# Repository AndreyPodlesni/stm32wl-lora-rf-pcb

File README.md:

# STM32WL LoRa RF PCB (KiCad)

## Overview
This is a 4-layer PCB design of a LoRa sensor node based on the STM32WLE5CCU6.  
It includes a temperature and humidity sensor (HDC2022) and an RF path to an SMA antenna.  
The board was designed in KiCad with focus on a working hardware setup and easy bring-up.  
The RF section follows the STM32WL development board schematics and layout guidelines.

---

## PCB Layout

---

## Key Features  
- STM32WLE5CCU6 (LoRa MCU)  
- HDC2022 temperature & humidity sensor  
- SMA antenna interface  
- 4-layer PCB  
- Battery powered (CR123A)  
- SWD debug interface + UART pins  

---

## Hardware Blocks  
  
### MCU  
STM32WLE5CCU6 with integrated Sub-GHz radio (LoRa).  
Combines MCU and RF transceiver in a single chip, reducing external components and simplifying the design.  

---

### RF Path  
- RF output from the MCU is routed through a matching network to an SMA antenna  
- RF routing implemented as a 50Ω microstrip based on PCB stackup calculations  
- Matching network includes optional components for antenna tuning  

---

### Sensor  
HDC2022 connected over I²C for temperature and humidity measurement  

---

### Battery  
CR123A lithium battery used as the main power source  

Selected for its ability to handle LoRa transmission current peaks and provide reliable long-term operation in a low-duty-cycle system  

Estimated battery life is over 2 years, based on power estimation using STM32CubeMX Power Consumption Calculator  

---

### Debug  
SWD interface and UART pins for programming and debugging  

---

## RF Notes
- RF traces routed as 50Ω controlled impedance  
- Microstrip routing over solid ground plane  
- RF path kept on a single layer (no vias)  

---

## Design Notes
- Matching network allows antenna tuning during testing  
- Battery selected to support LoRa current peaks  
- Power path prevents back-powering during debugging  

---
## Future Improvements
- Refine RF impedance control by considering copper pour clearance and surrounding geometry
- Improve sensor placement to reduce thermal influence from other components
- Further layout optimization for production readiness

## Tools
- KiCad 9  

---

## License
MIT

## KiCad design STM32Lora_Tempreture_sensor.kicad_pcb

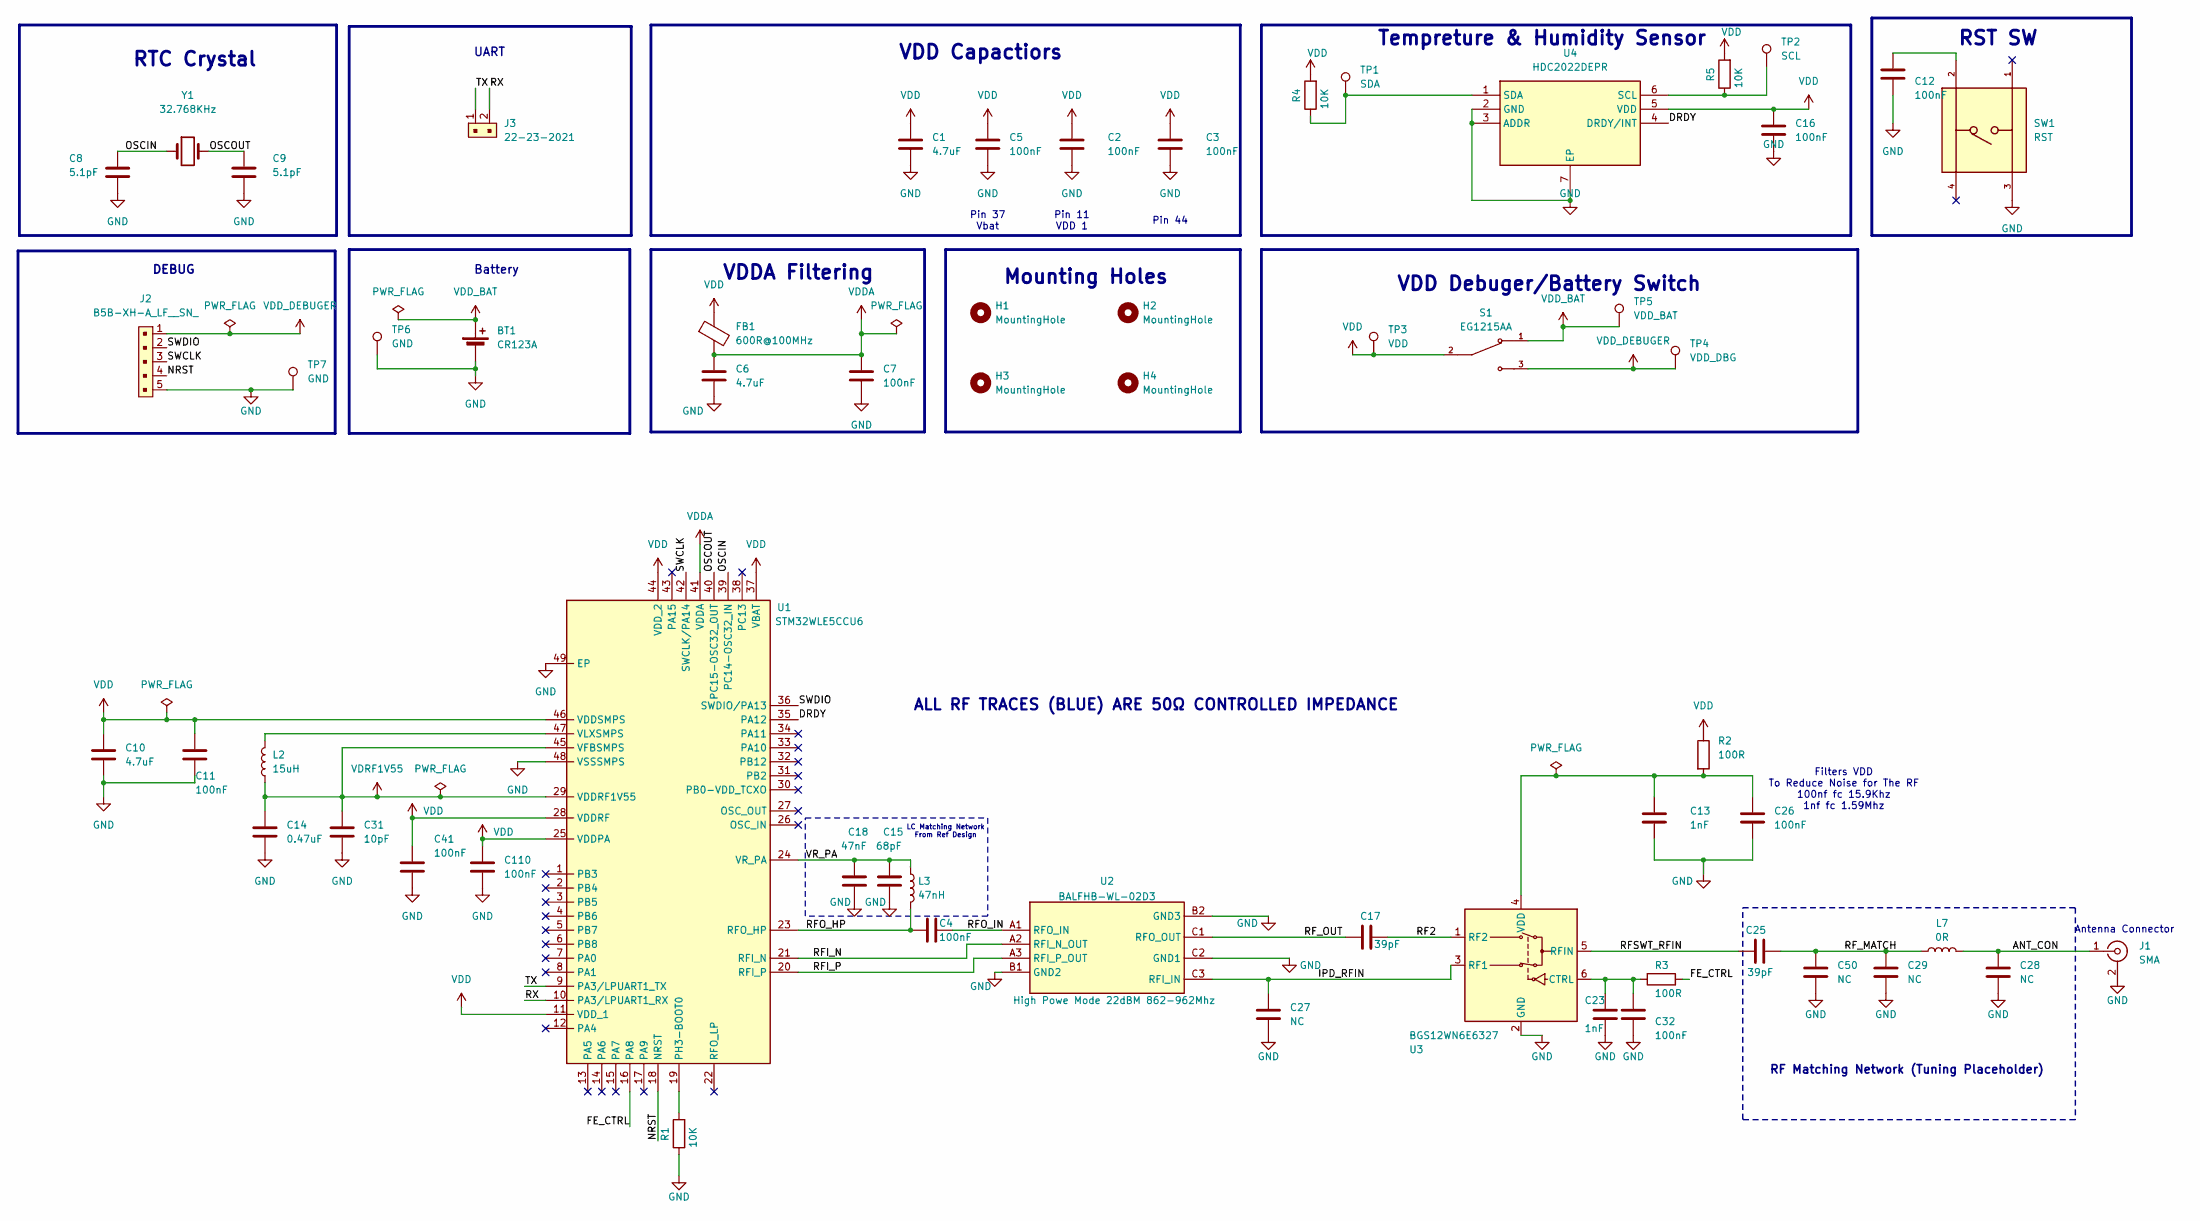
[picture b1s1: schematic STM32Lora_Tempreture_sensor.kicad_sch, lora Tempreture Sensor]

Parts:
BT1: CR123A; BAT_1050
C1, C6, C10: 4.7uF; C_0603_1608Metric
C2, C3, C4, C5, C7, C11, C12, C16, C26, C32, C41, C110: 100nF; C_0402_1005Metric
C8, C9: 5.1pF; C_0402_1005Metric
C13, C23: 1nF; C_0201_0603Metric
C14: 0.47uF; C_0603_1608Metric
C15: 68pF; C_0402_1005Metric
C17, C25: 39pF; C_0201_0603Metric
C18: 47nF; C_0402_1005Metric
C27, C28, C29, C50: NC; C_0201_0603Metric
C31: 10pF; C_0201_0603Metric
FB1: 600R@100MHz; BEADC1608X95N
H1, H2, H3, H4: MountingHole; MountingHole_2.2mm_M2_ISO14580
J1: SMA; SAMTEC_SMA-J-P-H-ST-EM1
J2: B5B-XH-A_LF__SN_; PinHeader_1x5_P2.5mm_Drill1.1mm; MPN B5B-XH-A(LF)(SN); Digi-Key_PN 455-2270-ND
J3: 22-23-2021; PinHeader_1x2_P2.54mm_Drill1.02mm; MPN 22-23-2021; Digi-Key_PN WM4200-ND
L2: 15uH; L_0805_2012Metric
L3: 47nH; L_0402_1005Metric
L7: 0R; L_0201_0603Metric
R1, R4, R5: 10K; R_0603_1608Metric
R2: 100R; R_0201_0603Metric
R3: 100R; R_0201_0603Metric_Pad0.64x0.40mm_HandSolder
S1: EG1215AA; SW_EG1215AA; PARTREV A
SW1: RST; Switch_Tactile_SMD_6x6mm; PARTREV 1.0
TP1: SDA; TestPoint_Pad_D1.0mm
TP2: SCL; TestPoint_Pad_D1.0mm
TP3: VDD; TestPoint_Pad_D1.0mm
TP4: VDD_DBG; TestPoint_Pad_D1.0mm
TP5: VDD_BAT; TestPoint_Pad_D1.0mm
TP6, TP7: GND; TestPoint_Pad_D1.0mm
U1: STM32WLE5CCU6; QFN50P700X700X60-49N-D; Manufacturer_Part_Number STM32WLE5CCU6; Mouser Part Number 511-STM32WLE5CCU6
U2: BALFHB-WL-02D3; BALFHBWL02D3; Mouser Part Number 511-BALFHB-WL-02D3
U3: BGS12WN6E6327; Infineon_PG-TSNP-6-10_0.7x1.1mm_0.7x1.1mm_P0.4mm
U4: HDC2022DEPR; SON100P300X300X115-7N-D; Mouser Part Number 595-HDC2022DEPR
Y1: 32.768KHz; NX2012SA32768KSTDMUB1

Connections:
/ANT_CON: C28.1, J1.1 (In), L7.2
/DRDY: U1.35 (PA12), U4.4 (DRDY/INT)
/FE_CTRL: R3.1, U1.16 (PA8)
/IPD_RFIN: C27.1, U2.C3 (RFI_IN), U3.3 (RF1)
/OSCIN: C8.1, U1.39 (PC14-OSC32_IN), Y1.1
/OSCOUT: C9.1, U1.40 (PC15-OSC32_OUT), Y1.2
/RF2: C17.2, U3.1 (RF2)
/RFI_N: U1.21 (RFI_N), U2.A2 (RFI_N_OUT)
/RFI_P: U1.20 (RFI_P), U2.A3 (RFI_P_OUT)
/RFO_HP: C4.1, L3.2, U1.23 (RFO_HP)
/RFO_IN: C4.2, U2.A1 (RFO_IN)
/RFSWT_RFIN: C25.1, U3.5 (RFIN)
/RF_MATCH: C25.2, C29.1, C50.1, L7.1
/RF_OUT: C17.1, U2.C1 (RFO_OUT)
/RX: J3.2, U1.10 (PA3/LPUART1_RX)
/SWCLK: J2.3, U1.42 (SWCLK/PA14)
/SWDIO: J2.2, U1.36 (SWDIO/PA13)
/TX: J3.1, U1.9 (PA3/LPUART1_TX)
/VR_PA: C15.1, C18.1, L3.1, U1.24 (VR_PA)
GND: BT1.N (-), C1.2, C2.2, C3.2, C5.2, C6.2, C7.2, C8.2, C9.2, C10.2, C11.2, C12.2, C13.2, C14.2, C15.2, C16.2, C18.2, C23.2, C26.2, C27.2, C28.2, C29.2, C31.2, C32.2, C41.2, C50.2, C110.2, J1.2 (Ext), J2.5, R1.1, SW1.3, TP6.1, TP7.1, U1.48 (VSSSMPS), U1.49 (EP), U2.B1 (GND2), U2.B2 (GND3), U2.C2 (GND1), U3.2 (GND), U4.2 (GND), U4.3 (ADDR), U4.7 (EP)
unnamed: R1.2, U1.19 (PH3-BOOT0)
unnamed: L2.2, U1.47 (VLXSMPS)
unnamed: C23.1, C32.1, R3.2, U3.6 (CTRL)
unnamed: C13.1, C26.1, R2.2, U3.4 (VDD)
unnamed: R5.1, TP2.1, U4.6 (SCL)
unnamed: R4.1, TP1.1, U4.1 (SDA)
VDD: C1.1, C2.1, C3.1, C5.1, C10.1, C11.1, C16.1, C41.1, C110.1, FB1.1, R2.1, R4.2, R5.2, S1.2, TP3.1, U1.11 (VDD_1), U1.25 (VDDPA), U1.28 (VDDRF), U1.37 (VBAT), U1.44 (VDD_2), U1.46 (VDDSMPS), U4.5 (VDD)
VDDA: C6.1, C7.1, FB1.2, U1.41 (VDDA)
VDD_BAT: BT1.P (+), S1.1, TP5.1
VDD_DEBUGER: J2.1, S1.3, TP4.1
VDRF1V55: C14.1, C31.1, L2.1, U1.29 (VDDRF1V55), U1.45 (VFBSMPS)

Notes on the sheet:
Pin 37 Vbat
RTC Crystal
Filters VDD To Reduce Noise for The RF 100nf fc 15.9Khz 1nf fc 1.59Mhz
VDD Debuger/Battery Switch
ALL RF TRACES (BLUE) ARE 50Ω CONTROLLED IMPEDANCE
UART
Pin 44
Antenna Connector
Battery
LC Matching Network From Ref Design
Mounting Holes
VDDA Filtering
RF Matching Network (Tuning Placeholder)
DEBUG
RST SW
VDD Capactiors
Pin 11 VDD 1
Tempreture & Humidity Sensor

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
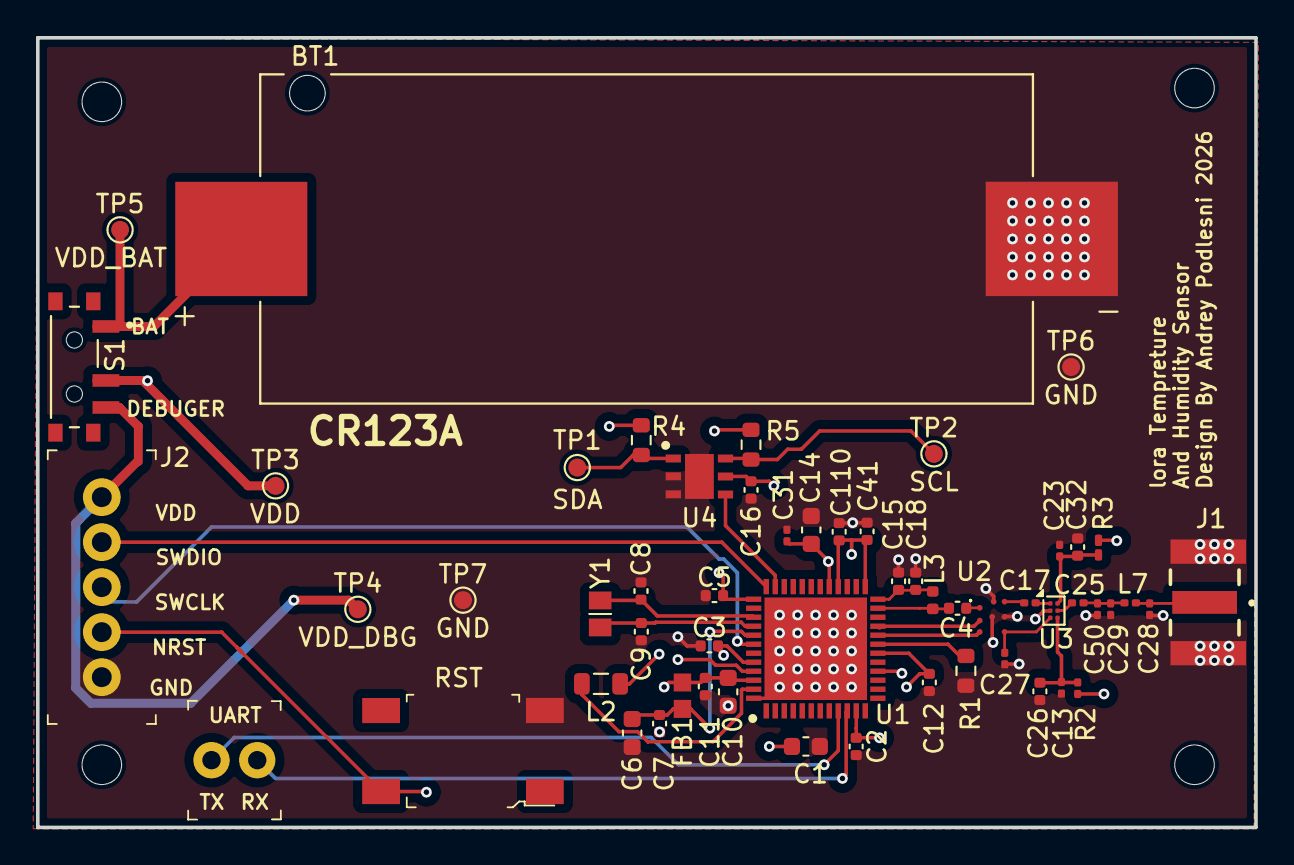
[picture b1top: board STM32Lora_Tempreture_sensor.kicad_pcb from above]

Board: 4 copper layers, 67.7 x 43.9 mm, 60 parts (0 on the bottom side), 32 nets.

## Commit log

2026-04-18 Files Added
